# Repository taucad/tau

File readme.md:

# Tau

Open-source, AI-native CAD: browser-based and kernel-agnostic. Design anything from 3D prints, game assets, and more.

**[Try it now at tau.new](https://tau.new)**

<picture>
  <source media="(prefers-color-scheme: dark)" srcset="docs/assets/tau-desktop-dark.webp">
  <source media="(prefers-color-scheme: light)" srcset="docs/assets/tau-desktop-light.webp">
  
</picture>

## Features

- **Open Source** — Apache-2.0 across the complete Tau codebase (see [Licensing](docs/licensing/overview.md))
- **Browser-Based** — Run CAD on mobile or desktop, no **installation** required
- **Code-Based CAD** — Precise, version-controlled designs through code
- **AI-Powered** — Natural language interface for design creation and modification
- **Parametric Editor** — Adjustable parameters with real-time preview
- **Multi-Kernel** — Choose the right CAD engine for your project
- **Embeddable** — Components to bring CAD into any web application
- **Runs Outside Tau** — Every project keeps its ecosystem's own files (`package.json`, `pyproject.toml`, a `.csproj`), so it runs with `npm ci`, `uv`, `dotnet`, OpenSCAD or the Zoo CLI; the standalone-project jobs ([Linux](https://github.com/taucad/tau/actions/workflows/ci.yml?query=branch%3Amain), [macOS](https://github.com/taucad/tau/actions/workflows/native-darwin.yml?query=branch%3Amain); sources [ci.yml](.github/workflows/ci.yml), [native-darwin.yml](.github/workflows/native-darwin.yml)) check each template against Tau's own export on every push to `main`

## Use Cases

- **3D Printing** — Design and export to STL, 3MF, and slicer-compatible formats
- **Game Development** — Create 3D models for games and simulations
- **Industrial Design** — Create 3D models for industrial design and manufacturing
- **CAD Prototyping** — Parametric code with version control and instant iteration
- **Academic Research** — Kernel APIs for computational geometry and educational tools

## Supported Integrations

Tau's multi-kernel architecture lets you choose the best engine for your needs. We support mechanical CAD and electrical design, with plans to expand into firmware development and simulation.

| Category       | Type | Implemented                                                                                                                                                                                                                                                                                                                                                                                                                                                                                                                                                   | Planned                                                                                                                                                                                                                               |
| -------------- | ---- | ------------------------------------------------------------------------------------------------------------------------------------------------------------------------------------------------------------------------------------------------------------------------------------------------------------------------------------------------------------------------------------------------------------------------------------------------------------------------------------------------------------------------------------------------------------- | ------------------------------------------------------------------------------------------------------------------------------------------------------------------------------------------------------------------------------------- |
| **Mechanical** | CAD  | • [OpenRSCAD](./packages/plugins/openrscad)<br>• [Replicad](https://replicad.xyz/)<br>• [Manifold](https://github.com/elalish/manifold)<br>• [Zoo (KCL)](https://zoo.dev/)<br>• [JSCAD](https://openjscad.xyz/)<br>• [OpenCascade](https://ocjs.org/) (direct [`libcascade`](https://www.npmjs.com/package/libcascade))<br>• [Build123D](https://github.com/gumyr/build123d) (Desktop)<br>• [PicoGK](https://github.com/leap71/PicoGK) ([ShapeKernel](https://github.com/leap71/LEAP71_ShapeKernel)) (Desktop)<br>• [PicoVoxel](./packages/plugins/picovoxel) | • [OnShape](https://www.onshape.com/)<br>• [Fusion360](https://www.autodesk.com/products/fusion-360)<br>• [Curv](https://github.com/curv3d/curv)<br>• [ClassCAD](https://classcad.ch/)<br>• [Truck](https://github.com/ricosjp/truck) |
|                | Sim  | —                                                                                                                                                                                                                                                                                                                                                                                                                                                                                                                                                             | • [FEAScript](https://feascript.com/)                                                                                                                                                                                                 |
| **Electrical** | CAD  | • [TSCircuit](https://tscircuit.com/)                                                                                                                                                                                                                                                                                                                                                                                                                                                                                                                         | • [Atopile](https://atopile.io/)                                                                                                                                                                                                      |
|                | Sim  | —                                                                                                                                                                                                                                                                                                                                                                                                                                                                                                                                                             | • [ngspice](https://ngspice.sourceforge.io/)<br>• [CircuitJS](https://www.falstad.com/circuit/)                                                                                                                                       |
| **Firmware**   | CAD  | —                                                                                                                                                                                                                                                                                                                                                                                                                                                                                                                                                             | • [Arduino](https://www.arduino.cc/)<br>• [MicroPython](https://micropython.org/)                                                                                                                                                     |
|                | Sim  | —                                                                                                                                                                                                                                                                                                                                                                                                                                                                                                                                                             | • [QEMU](https://www.qemu.org/)<br>• [Wokwi](https://wokwi.com/)                                                                                                                                                                      |

## File Converter

Convert between **39 input formats** and **14 output formats** including STL, STEP, GLTF, FBX, 3MF, OBJ, USDZ, and more.

## Community

- **Discord** — [Join our community](https://discord.gg/6pfSAN3t7A)
- **Documentation** — [tau.new/docs](https://tau.new/docs)
- **GitHub Discussions** — Ask questions and share ideas

## Contributing

We welcome contributions! Please see our [Contributing Guide](.github/CONTRIBUTING.md) for development setup and guidelines.

## Security

For security concerns, please review our [Security Policy](.github/SECURITY.md).

## Code of Conduct

Please read our [Code of Conduct](.github/CODE_OF_CONDUCT.md) before participating.

## Built With

Tau is built on a foundation of excellent open-source projects:

| Category             | Technologies                                                                                                                                                                                   |
| -------------------- | ---------------------------------------------------------------------------------------------------------------------------------------------------------------------------------------------- |
| **State Management** | [XState v6](https://stately.ai/docs)                                                                                                                                                           |
| **UI Framework**     | [React 19](https://react.dev/), [React Router](https://reactrouter.com/), [Radix UI](https://www.radix-ui.com/), [shadcn/ui](https://ui.shadcn.com/), [Tailwind CSS](https://tailwindcss.com/) |
| **Workspace Layout** | [Dockview](https://dockview.dev/)                                                                                                                                                              |
| **Code Editor**      | [CodeMirror](https://codemirror.net/), [Lezer](https://lezer.codemirror.net/)                                                                                                                  |
| **3D Rendering**     | [Three.js](https://threejs.org/), [React Three Fiber](https://r3f.docs.pmnd.rs/)                                                                                                               |
| **AI Agents**        | [Pi](https://github.com/earendil-works/pi), [AI SDK](https://ai-sdk.dev/)                                                                                                                      |
| **API**              | [NestJS](https://nestjs.com/), [Fastify](https://fastify.dev/), [Better Auth](https://www.better-auth.com/)                                                                                    |
| **Database**         | [Drizzle ORM](https://orm.drizzle.team/)                                                                                                                                                       |
| **Git Operations**   | [Isomorphic Git](https://isomorphic-git.org/)                                                                                                                                                  |
| **Desktop**          | [Electron](https://www.electronjs.org/)                                                                                                                                                        |

Special thanks to [OpenSCAD Playground](https://github.com/openscad/openscad-playground) for inspiring the browser-based code-CAD architecture.

## License

All Tau-authored code is **[Apache-2.0](license)**, including the applications, internal libraries, tools, examples,
published packages, and the GeoSpec engine. It may be forked, modified, embedded, hosted, and redistributed, including
commercially, subject to the Apache licence and notice requirements.

See **[Licensing](docs/licensing/overview.md)** for repository-wide details, previous-release treatment, and third-party notices.

Full third-party license inventory: [third-party licenses](docs/licensing/third-party-licenses.md).

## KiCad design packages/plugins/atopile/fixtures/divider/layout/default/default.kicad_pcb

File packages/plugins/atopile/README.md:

# @taucad/atopile

atopile EDA kernel for Tau: .ato circuits compiled by atopile and rendered to 3D boards, schematic and PCB SVG, with BOM exports

## Why @taucad/atopile?

- **One call composes it** — `atopile()` registers this package's capabilities with `defineRuntime`.
- **Role factories** — `atopileKernel()` support direct authoring, isolated tests, and whole-role ordering outside plugin expansion.
- **No module-scope work** — backends load in `initialize()` and stay in capability context, one payload per worker.

## Install

```bash
npm i @taucad/atopile @taucad/runtime
```

`@taucad/runtime` is a required peer — one install must hold one runtime. A capability with an options
schema adds `zod` as a second required peer.

> **Spike.** This package proves that atopile 0.15.x projects render in Tau. It runs atopile as a
> subprocess of an interpreter you supply and is not wired into any Tau host yet. Production work is
> tracked in `docs/research/atopile-kernel-production-blueprint.md`.

## Requirements

- CPython 3.14 with `atopile` 0.15.x installed (`uv venv -p 3.14 && uv pip install atopile==0.15.9`).
- Parts vendored as atomic parts under `parts/` (what `ato create part` writes). Parametric parts such as
  a bare `Resistor` need atopile's signed-in picker service; the kernel reports that as an issue.
- No KiCad install: Tau renders every view itself.

## Quick start

```typescript
import { defineRuntime } from '@taucad/runtime/worker';
import { atopile } from '@taucad/atopile';

const runtime = defineRuntime({
  plugins: [atopile({ kernels: { default: { python: '/path/to/venv/bin/python' } } })],
});
```

Without the `python` option the kernel uses `TAU_ATOPILE_PYTHON`, then `python3`.

## Views and exports

| Kind   | ID          | Output                                                                    |
| ------ | ----------- | ------------------------------------------------------------------------- |
| View   | `board`     | GLB board with each footprint's STEP model                                |
| View   | `schematic` | Schematic SVG laid out by `@tscircuit/core` from atopile's netlist        |
| View   | `pcb`       | PCB SVG at the KiCad layout's positions (packed when the layout is fresh) |
| Export | `board`     | `board.glb`                                                               |
| Export | `bom`       | `bom.csv` from atopile's own BOM (designators, MPN, LCSC part numbers)    |
| Export | `netlist`   | `netlist.txt`                                                             |
| Export | `circuit`   | `circuit.json`                                                            |
| Export | `kicad`     | `<build>.kicad_pcb` as atopile wrote it                                   |

## How it works

1. The kernel mirrors the project (the nearest directory holding `ato.yaml`) into a private temporary directory.
2. `python/atopile_worker.py` runs `ato build --target bom` there and prints a board IR: footprints, pads,
   nets, the board outline, embedded STEP models and atopile's BOM rows.
3. The kernel settles the IR through `@tscircuit/core` into circuit JSON, which `circuit-to-svg` and
   `circuit-json-to-gltf` render, exactly as `@taucad/tscircuit` does.

Hand the definition to a client — `createNodeClient`, `createRuntimeWorker`, or your own host. See
[`@taucad/runtime`](https://www.npmjs.com/package/@taucad/runtime) for the client lifecycle.

## API

| Export          | Kind            | Use                                                                           |
| --------------- | --------------- | ----------------------------------------------------------------------------- |
| `atopile`       | toolkit factory | package-named authoring factory; presets select capabilities                  |
| `plugin`        | toolkit factory | the same factory under its mechanical name, for loaders that read a fixed key |
| `atopileKernel` | kernel factory  | direct `kernels` composition, with options                                    |

One preset, `default`, selecting `kernels.default`.

## Environment

| Host           | Supported | Notes                                                        |
| -------------- | --------- | ------------------------------------------------------------ |
| Browser worker | No        | `taucad.hostTarget: node` — this package is not browser-safe |
| Node.js        | Yes       | `>=24`                                                       |

## Versioning and stability

Pre-1.0: a minor version may break. Pin `~0.1.0` rather than `^0.1.0`. This package releases in the
fixed version group with `@taucad/runtime`, so the peer range always matches a published runtime.
See [version-policy.md](https://github.com/taucad/tau/blob/main/docs/policy/version-policy.md).

## Security and provenance

Every release is published from GitHub Actions with npm trusted publishing and
[provenance](https://docs.npmjs.com/generating-provenance-statements). Verify a downloaded tree:

```bash
npm audit signatures
```

## License

Apache-2.0 — see [LICENSE](./LICENSE). Bundled third-party payloads keep their own licenses.

## Links

- [Documentation](https://tau.new/docs/runtime)
- [Source](https://github.com/taucad/tau/tree/main/packages/plugins/atopile)
- [Changelog](https://github.com/taucad/tau/blob/main/packages/plugins/atopile/CHANGELOG.md)
- [Issues](https://github.com/taucad/tau/issues)

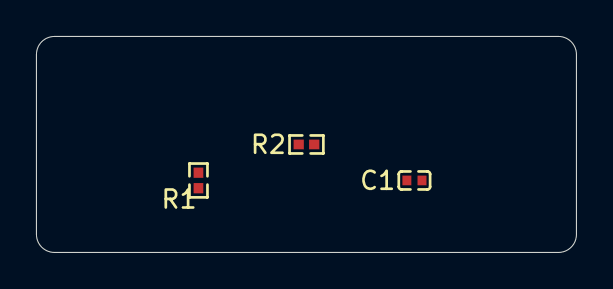
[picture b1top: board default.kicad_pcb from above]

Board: 2 copper layers, 30.0 x 12.0 mm, 3 parts (0 on the bottom side), 2 nets, no tracks yet.

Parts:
C1: C0402
R1, R2: R0402

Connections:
lv: C1.2, R1.2
output: C1.1, R1.1, R2.2
